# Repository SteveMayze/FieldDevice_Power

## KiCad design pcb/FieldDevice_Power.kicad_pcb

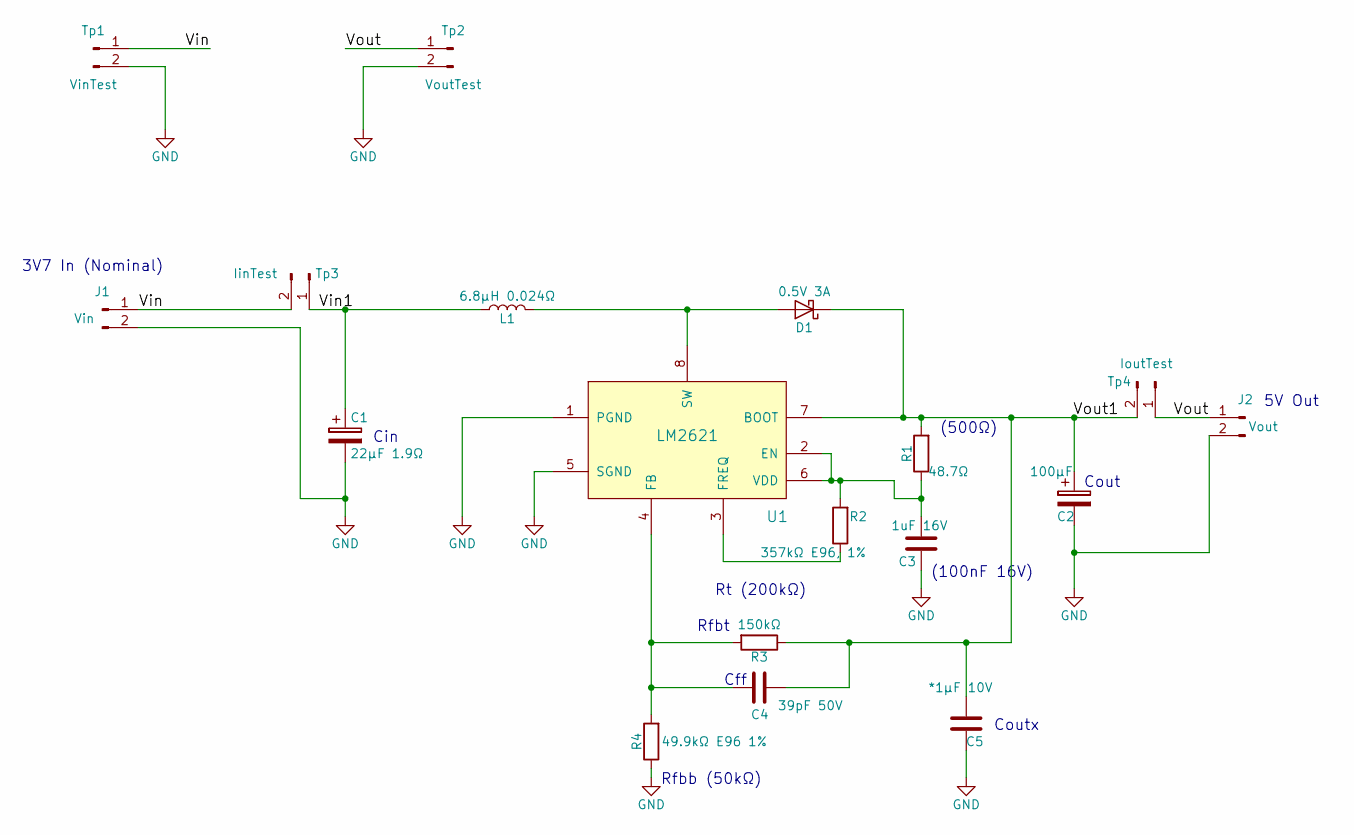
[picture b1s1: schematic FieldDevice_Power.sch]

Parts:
C1: 22μF 1.9Ω; CP_Tantalum_Case-B_EIA-3528-21_Hand; MPN 293D226X9016B2TE3
C2: 100μF; CP_Tantalum_Case-D_EIA-7343-31_Hand; MPN 593D107X0010D2TE3
C3: 1uF 16V; C_0805_HandSoldering; MPN EMK212B7105KG-T
C4: 39pF 50V; C_0805_HandSoldering; MPN CC0805JRNPO9BN390
C5: *1μF 10V; C_0603_HandSoldering; MPN C0603C105Z8VACTU
D1: 0.5V 3A; D_SMA_Handsoldering; MPN B320A-13-F
J1: Vin; Pin_Header_Straight_1x02_Pitch2.54mm
J2: Vout; Pin_Header_Straight_1x02_Pitch2.54mm
L1: 6.8μH 0.024Ω; INDUCTOR_1255AY-6R8M=P3; MPN 1255AY-6R8M=P3
R1: 48.7Ω; R_0402; MPN CRCW040248R7FKED
R2: 357kΩ E96, 1%; R_0402; MPN CRCW0402357KFKED
R3: 150kΩ; R_0805_HandSoldering; MPN RR1220P-154-D
R4: 49.9kΩ E96 1%; R_0402; MPN RC0402FR-0749K9L
Tp1: VinTest; Pin_Header_Straight_1x02_Pitch2.54mm
Tp2: VoutTest; Pin_Header_Straight_1x02_Pitch2.54mm
Tp3: IinTest; Pin_Header_Straight_1x02_Pitch2.54mm
Tp4: IoutTest; Pin_Header_Straight_1x02_Pitch2.54mm
U1: LM2621; TSSOP-8_3x3mm_Pitch0.65mm; MPN LM2621MM/NOPB

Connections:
/Vin: J1.1, Tp1.1, Tp3.2
/Vin1: C1.1, L1.1, Tp3.1
/Vout: J2.1, Tp2.1, Tp4.1
/Vout1: C2.1, C4.1, C5.2, D1.1 (K), R1.2, R3.1, Tp4.2, U1.7 (BOOT)
GND: C1.2, C2.2, C3.1, C5.1, J1.2, J2.2, R4.1, Tp1.2, Tp2.2, U1.1 (PGND), U1.5 (SGND)
unnamed: C3.2, R1.1, R2.2, U1.2 (EN), U1.6 (VDD)
unnamed: C4.2, R3.2, R4.2, U1.4 (FB)
unnamed: D1.2 (A), L1.2, U1.8 (SW)
unnamed: R2.1, U1.3 (FREQ)

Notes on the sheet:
Rt (200kΩ)
(100nF 16V)
(500Ω)
Rfbb (50kΩ)
Cout
Coutx
Cff
Rfbt
Cin
5V Out
3V7 In (Nominal)

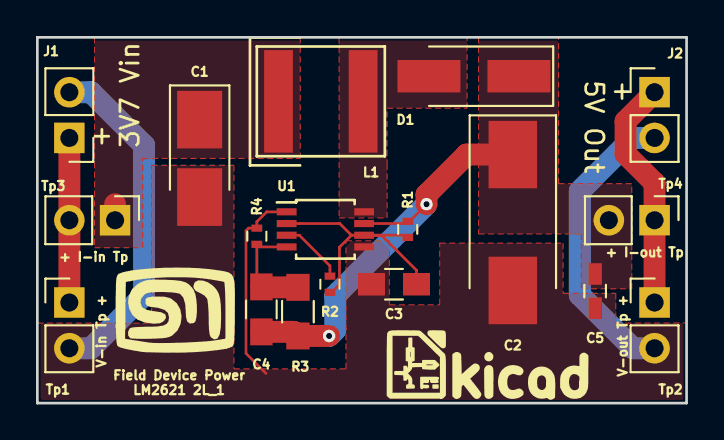
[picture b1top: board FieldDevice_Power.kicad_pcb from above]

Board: 2 copper layers, 36.1 x 20.3 mm, 18 parts (0 on the bottom side), 9 nets.

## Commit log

2017-10-31 First commit - including initial schematic and a start on the layout
2017-10-31 Added the pin headers for Vin and Vout
2017-11-01 Completed the layout and parts decisions
2017-11-01 Updated a replacement for R4
2017-11-26 Researching options for the charger and buckboost converter
